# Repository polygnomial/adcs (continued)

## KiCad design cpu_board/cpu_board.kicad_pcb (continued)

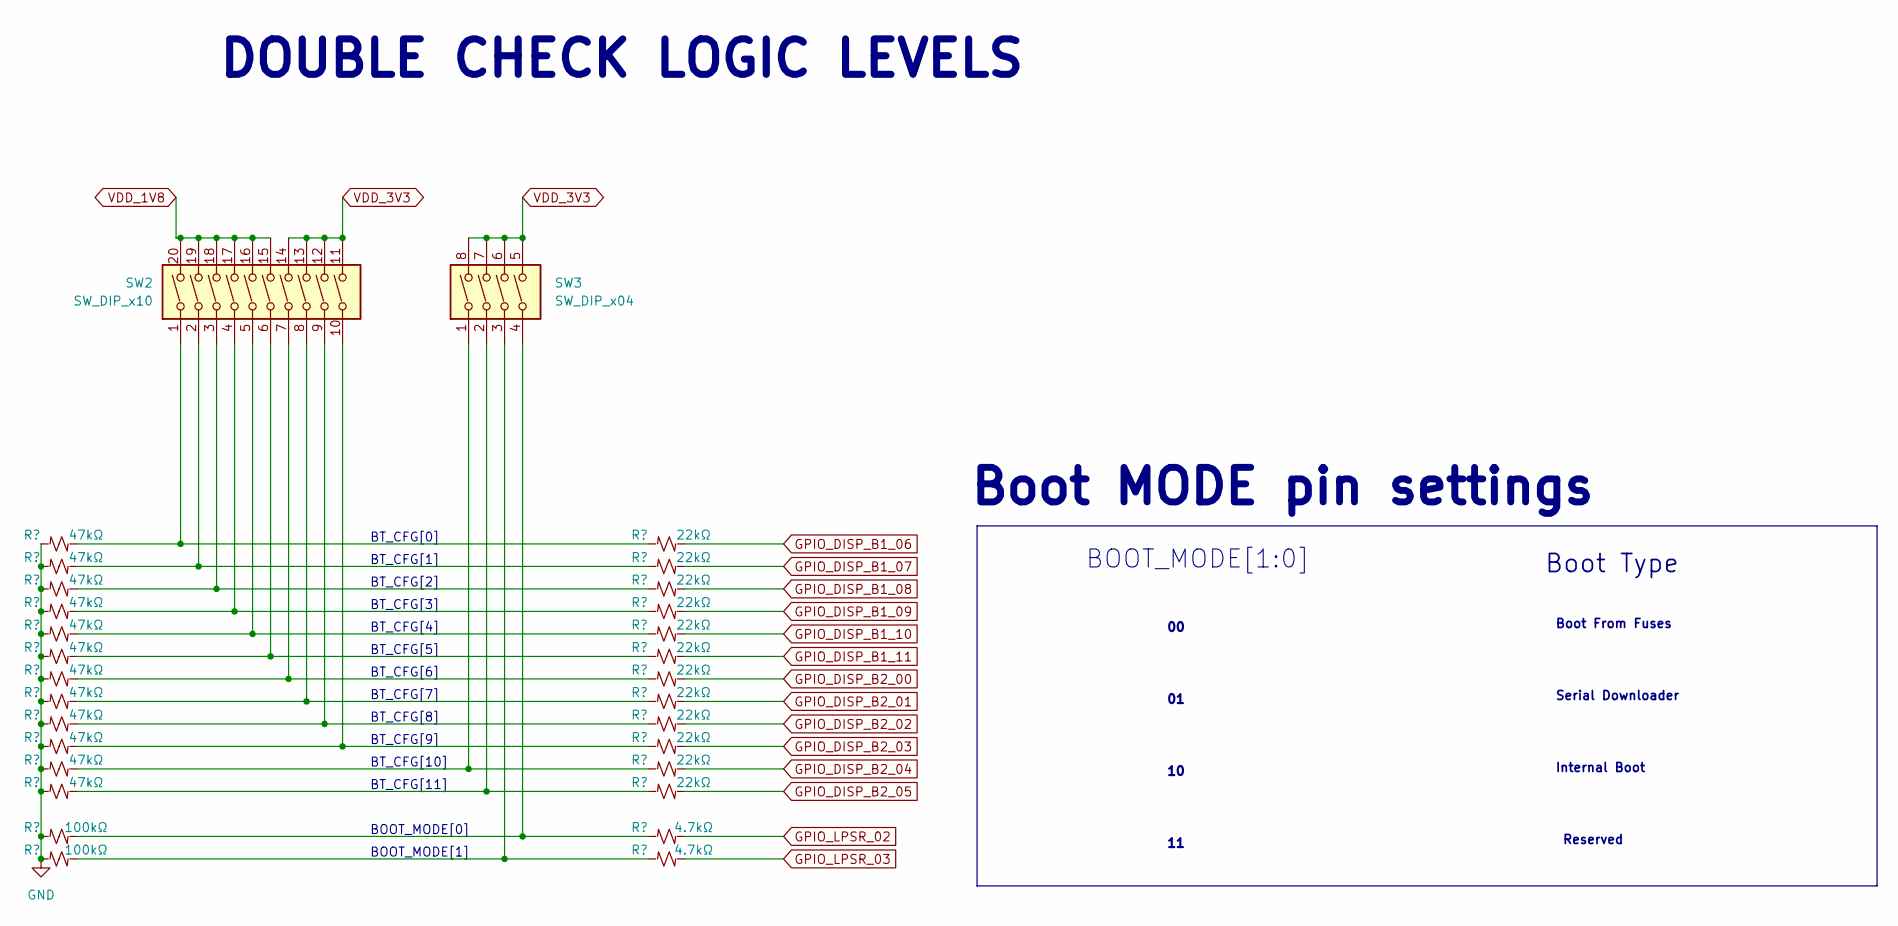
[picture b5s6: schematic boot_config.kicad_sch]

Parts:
R37, R38, R39, R40, R41, R42, R43, R44, R45, R46, R47, R48: 47kΩ; Perfect_0402
R49, R50: 100kΩ; Perfect_0402
R51, R52, R53, R54, R55, R56, R57, R58, R59, R60, R61, R62: 22kΩ; Perfect_0402
R63, R64: 4.7kΩ; Perfect_0402
SW2: SW_DIP_x10; SW-SMD_DSHP10TS-S; JLCPCB P/N Proto C319046
SW3: SW_DIP_x04; SW-SMD_8P-L6.7-W5.4-P1.27-LS8.5; JLCPCB P/N Proto C319050

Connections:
ENET_RGMII_TXC_BT: R56.2; also elsewhere on the board
ENET_RGMII_TXD0_BT: R54.2; also elsewhere on the board
ENET_RGMII_TXD1_BT: R53.2; also elsewhere on the board
ENET_RGMII_TXD2_BT: R52.2; also elsewhere on the board
ENET_RGMII_TXD3_BT: R51.2; also elsewhere on the board
ENET_RGMII_TX_EN_BT: R55.2; also elsewhere on the board
GPIO_DISP_B2_00: R57.2; also elsewhere on the board
GPIO_DISP_B2_01: R58.2; also elsewhere on the board
GPIO_DISP_B2_02: R59.2; also elsewhere on the board
GPIO_DISP_B2_03: R60.2; also elsewhere on the board
GPIO_DISP_B2_04: R61.2; also elsewhere on the board
GPIO_DISP_B2_05: R62.2; also elsewhere on the board
GPIO_LPSR_02: R63.2; also elsewhere on the board
GPIO_LPSR_03: R64.2; also elsewhere on the board
unnamed: R37.2, R51.1, SW2.1
unnamed: R38.2, R52.1, SW2.2
unnamed: R39.2, R53.1, SW2.3
unnamed: R40.2, R54.1, SW2.4
unnamed: R41.2, R55.1, SW2.5
unnamed: R42.2, R56.1, SW2.6
unnamed: R43.2, R57.1, SW2.7
unnamed: R44.2, R58.1, SW2.8
unnamed: R45.2, R59.1, SW2.9
unnamed: R46.2, R60.1, SW2.10
unnamed: R47.2, R61.1, SW3.1
unnamed: R48.2, R62.1, SW3.2
unnamed: R49.2, R63.1, SW3.4
unnamed: R50.2, R64.1, SW3.3
VDD_1V8: SW2.15, SW2.16, SW2.17, SW2.18, SW2.19, SW2.20; also elsewhere on the board
VDD_3V3: SW2.11, SW2.12, SW2.13, SW2.14, SW3.5, SW3.6, SW3.7, SW3.8; also elsewhere on the board

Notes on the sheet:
BOOT_MODE[1]
Internal Boot
DOUBLE CHECK LOGIC LEVELS
BT_CFG[10]
BT_CFG[6]
BT_CFG[8]
Serial Downloader
BT_CFG[2]
BT_CFG[4]
BT_CFG[9]
Boot From Fuses
BT_CFG[1]
Reserved
BT_CFG[0]
BT_CFG[11]
BOOT_MODE[1:0]
BT_CFG[5]
BOOT_MODE[0]
Boot Type
Boot MODE pin settings
BT_CFG[3]
BT_CFG[7]

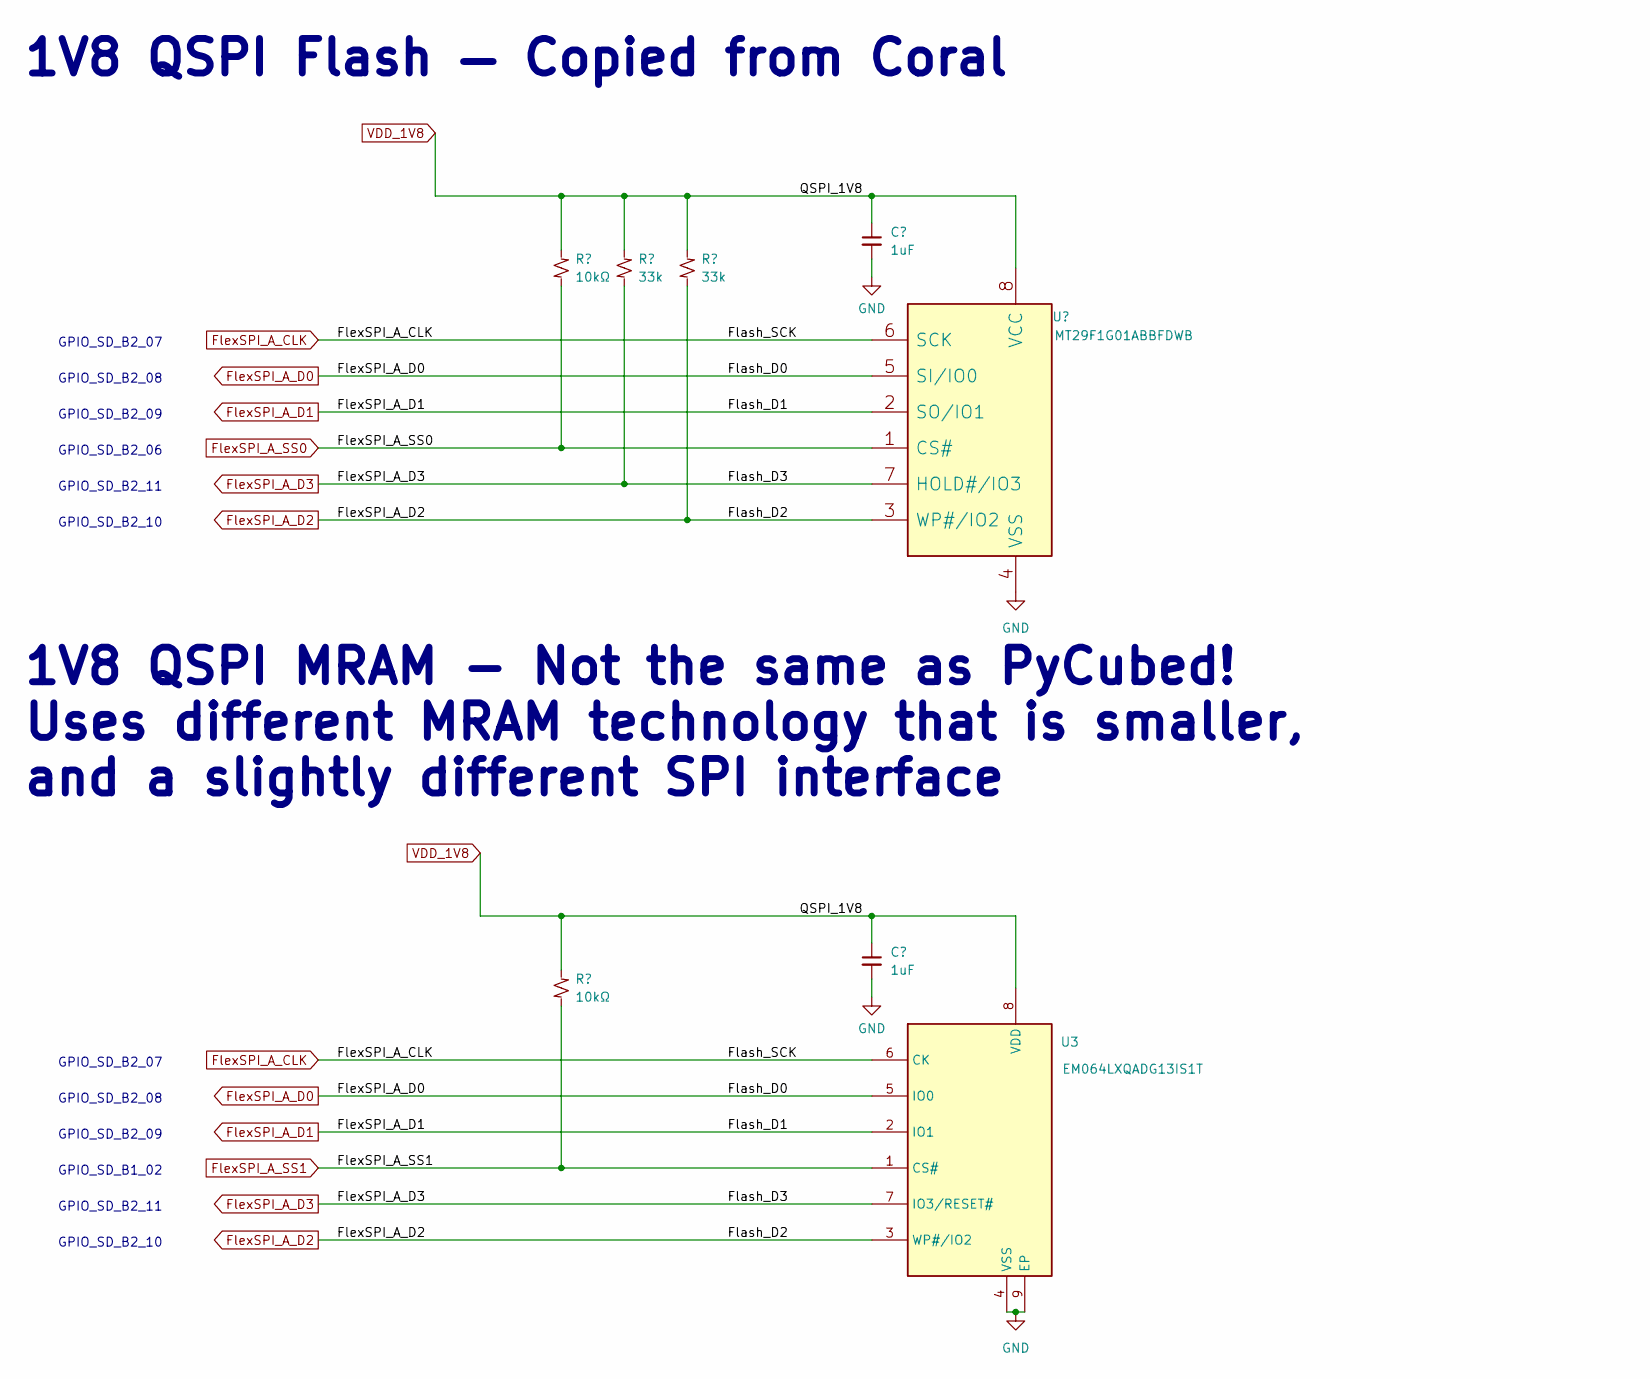
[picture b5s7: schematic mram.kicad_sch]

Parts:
C62, C63: 1uF; Perfect_0402
R16, R17: 10kΩ; Perfect_0402
R18, R20: 33k; Perfect_0402
U3: EM064LXQADG13IS1T; SON127P800X600X95-9N-D
U4: MT29F1G01ABBFDWB; UDFN800X600X65-8; JLCPCB P/N Proto C5330479

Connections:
FlexSPI_A_CLK: U3.6 (CK), U4.6 (SCK); also elsewhere on the board
FlexSPI_A_D0: U3.5 (IO0), U4.5 (SI/IO0); also elsewhere on the board
FlexSPI_A_D1: U3.2 (IO1), U4.2 (SO/IO1); also elsewhere on the board
FlexSPI_A_D2: R20.2, U3.3 (WP#/IO2), U4.3 (WP#/IO2); also elsewhere on the board
FlexSPI_A_D3: R18.2, U3.7 (IO3/RESET#), U4.7 (HOLD#/IO3); also elsewhere on the board
FlexSPI_A_SS0: R16.2, U4.1 (CS#); also elsewhere on the board
FlexSPI_A_SS1: R17.2, U3.1 (CS#); also elsewhere on the board
VDD_1V8: C62.1, C63.1, R16.1, R17.1, R18.1, R20.1, U3.8 (VDD), U4.8 (VCC); also elsewhere on the board

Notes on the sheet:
1V8 QSPI Flash — Copied from Coral
GPIO_SD_B2_10
1V8 QSPI MRAM - Not the same as PyCubed! Uses different MRAM technology that is smaller, and a slightly different SPI interface
GPIO_SD_B2_08
GPIO_SD_B2_06
GPIO_SD_B2_07
GPIO_SD_B1_02
GPIO_SD_B2_09
GPIO_SD_B2_11

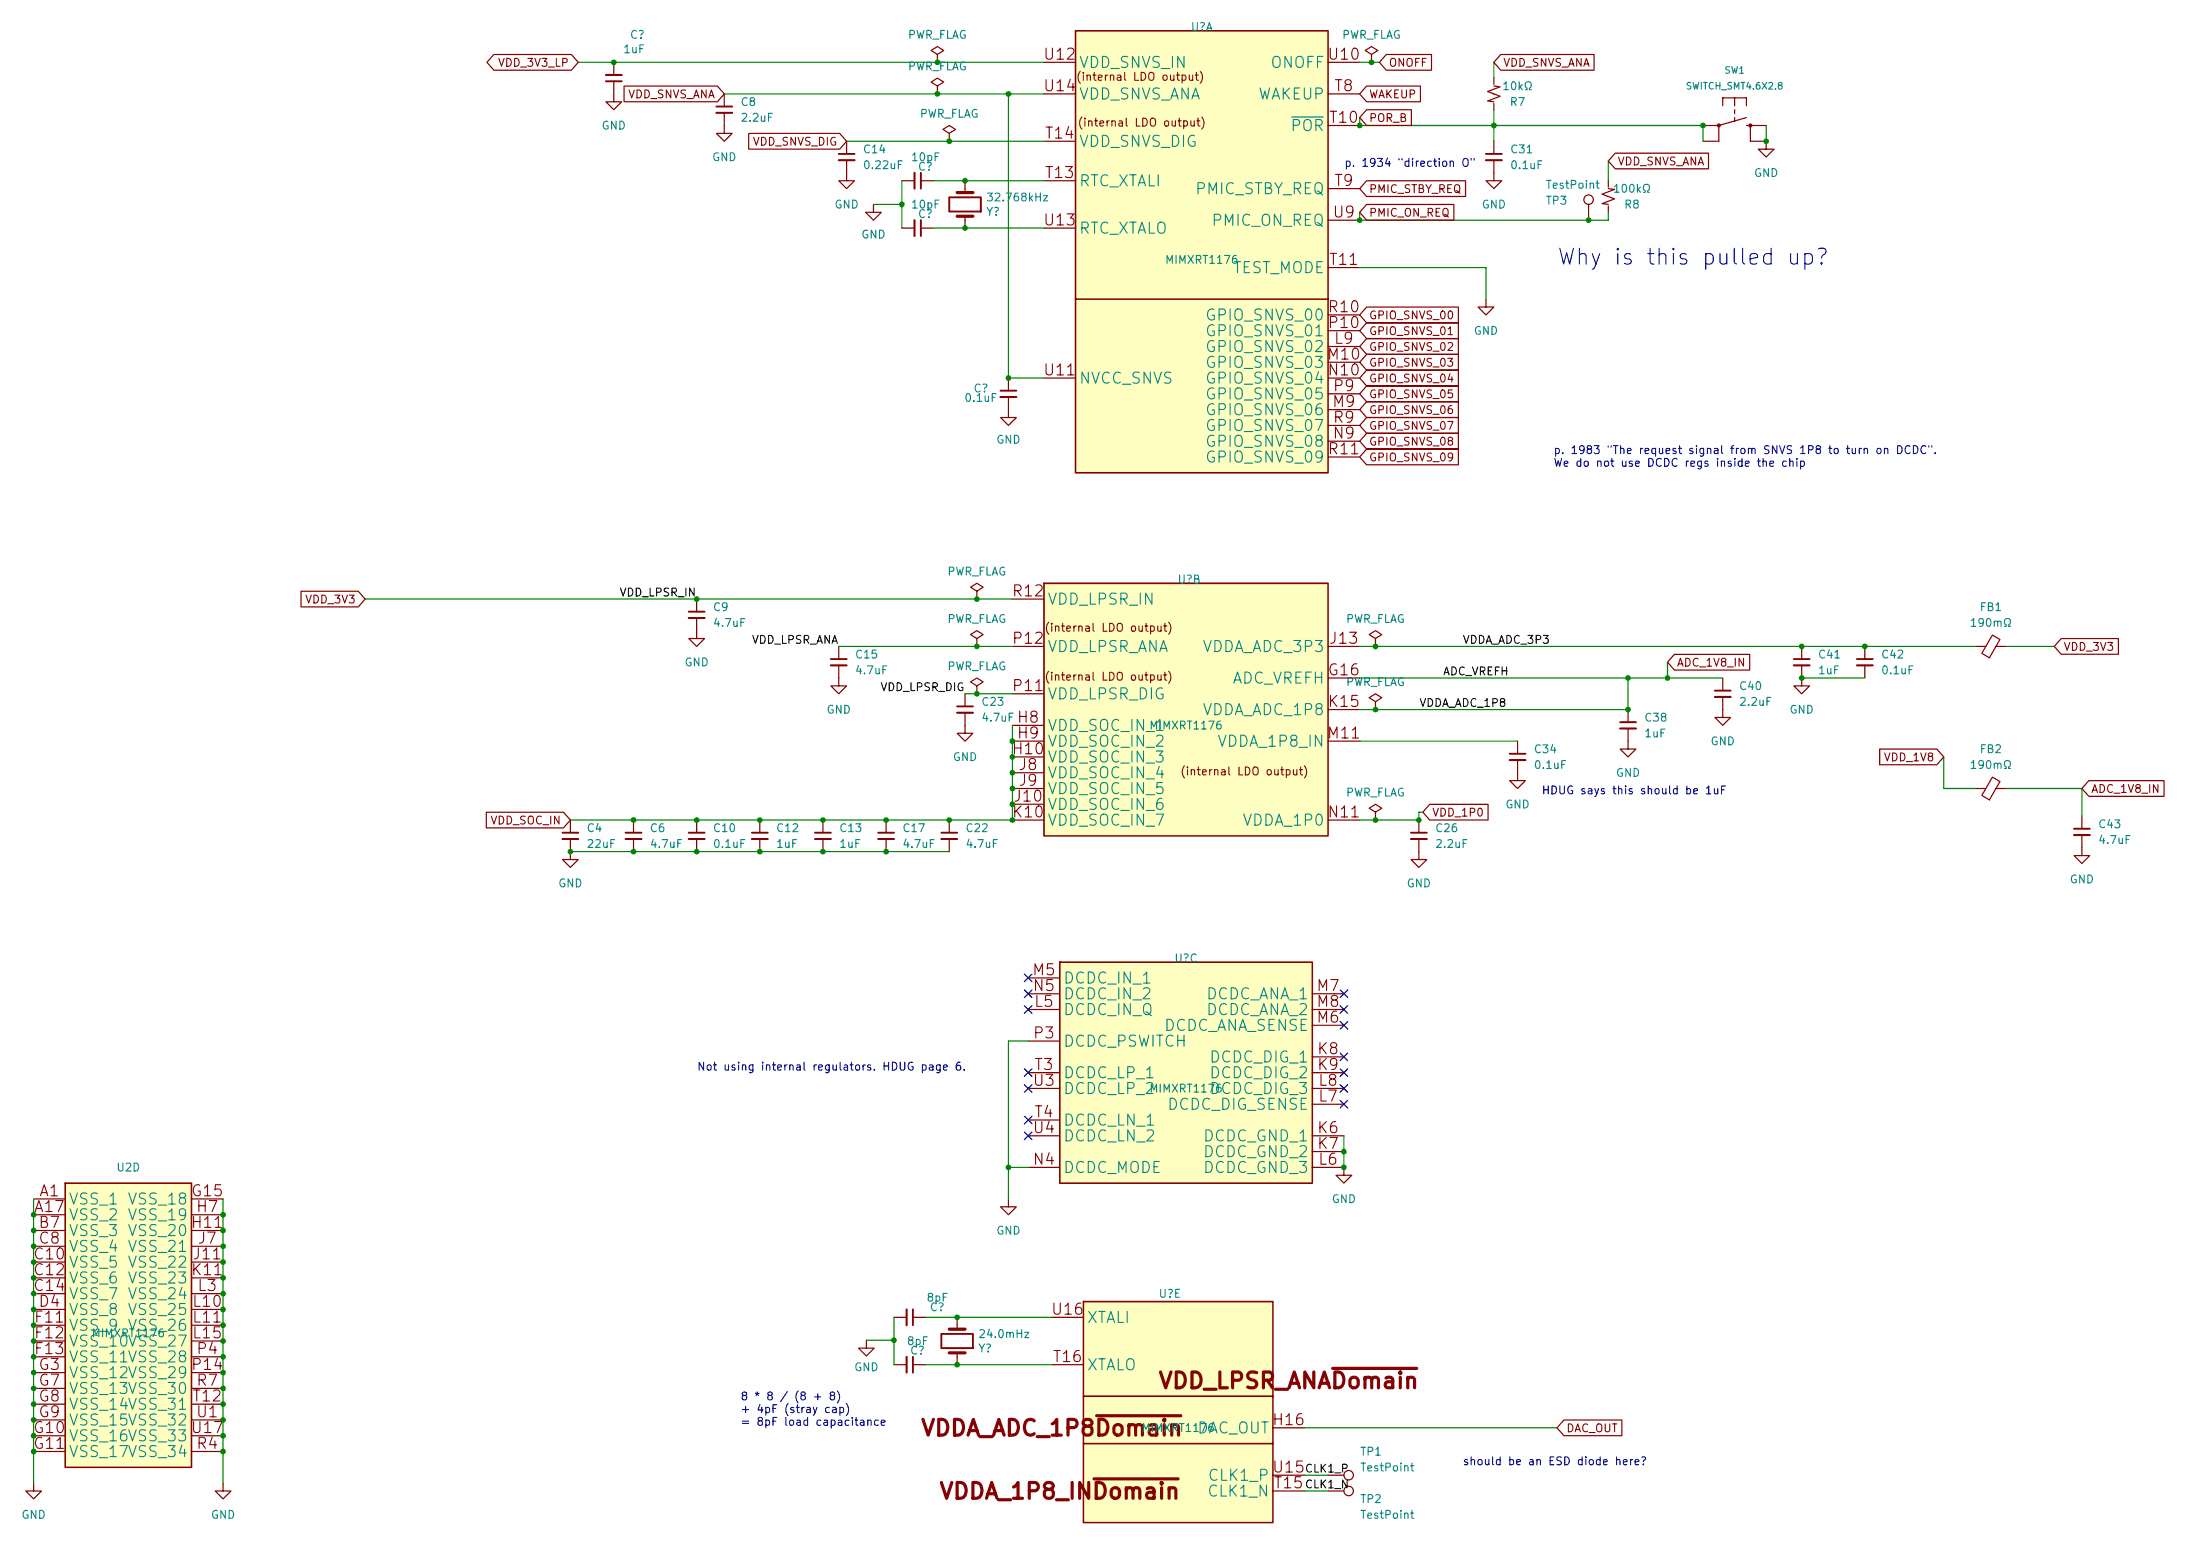
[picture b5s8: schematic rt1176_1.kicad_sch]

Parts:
C3, C12, C13, C38, C41: 1uF; Perfect_0201
C4: 22uF; C_0603_1608Metric
C6: 4.7uF; Perfect_0201; Voltage Rating 6.3V
C8, C26, C40: 2.2uF; Perfect_0201
C9, C15, C17, C22, C23, C43: 4.7uF; Perfect_0201
C10, C25, C34, C42: 0.1uF; Perfect_0201
C14: 0.22uF; Perfect_0201
C18, C19: 8pF; Perfect_0402
C20, C21: 10pF; Perfect_0402
C31: 0.1uF; Perfect_0402
FB1, FB2: 190mΩ; Perfect_0402; JLCPCB P/N C85812
R7: 10kΩ; Perfect_0402
R8: 100kΩ; Perfect_0402
SW1: SWITCH_SMT4.6X2.8; BTN_KMR2_4.6X2.8
TP1, TP2, TP3: TestPoint; TestPoint_Pad_1.0x1.0mm; JLCPCB P/N C221678
U2: MIMXRT1176; U_MIMXRT1176DVMAA_NXP; JLCPCB P/N C1020267
Y2: 24.0mHz; Crystal_SMD_2016-4Pin_2.0x1.6mm; JLCPCB P/N C1986107
Y3: 32.768kHz; Crystal_SMD_3215-2Pin_3.2x1.5mm; JLCPCB P/N C145140

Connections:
/RT1176 #1/CLK1_N: TP2.1, U2.T15 (CLK1_N)
/RT1176 #1/CLK1_P: TP1.1, U2.U15 (CLK1_P)
/RT1176 #1/VDDA_ADC_3P3: C41.1, C42.1, FB1.1, U2.J13 (VDDA_ADC_3P3)
/RT1176 #1/VDD_LPSR_ANA: C15.1, U2.P12 (VDD_LPSR_ANA)
/RT1176 #1/VDD_LPSR_DIG: C23.1, U2.P11 (VDD_LPSR_DIG)
ADC_1V8_IN: C38.1, C40.1, C43.1, FB2.2, U2.G16 (ADC_VREFH), U2.K15 (VDDA_ADC_1P8)
DAC_OUT: U2.H16 (DAC_OUT); also elsewhere on the board
GPIO_SNVS_00: U2.R10 (GPIO_SNVS_00); also elsewhere on the board
GPIO_SNVS_01: U2.P10 (GPIO_SNVS_01); also elsewhere on the board
GPIO_SNVS_02: U2.L9 (GPIO_SNVS_02); also elsewhere on the board
GPIO_SNVS_03: U2.M10 (GPIO_SNVS_03); also elsewhere on the board
GPIO_SNVS_04: U2.N10 (GPIO_SNVS_04); also elsewhere on the board
GPIO_SNVS_05: U2.P9 (GPIO_SNVS_05); also elsewhere on the board
GPIO_SNVS_06: U2.M9 (GPIO_SNVS_06); also elsewhere on the board
GPIO_SNVS_07: U2.R9 (GPIO_SNVS_07); also elsewhere on the board
GPIO_SNVS_08: U2.N9 (GPIO_SNVS_08); also elsewhere on the board
GPIO_SNVS_09: U2.R11 (GPIO_SNVS_09); also elsewhere on the board
unnamed: C20.1, U2.T13 (RTC_XTALI), Y3.2
unnamed: C21.1, U2.U13 (RTC_XTALO), Y3.1
unnamed: C34.1, U2.M11 (VDDA_1P8_IN)
unnamed: C18.1, U2.U16 (XTALI), Y2.2
unnamed: C19.1, U2.T16 (XTALO), Y2.1
ONOFF: U2.U10 (ONOFF); also elsewhere on the board
PMIC_ON_REQ: R8.1, TP3.1, U2.U9 (PMIC_ON_REQ); also elsewhere on the board
PMIC_STBY_REQ: U2.T9 (PMIC_STBY_REQ); also elsewhere on the board
POR_B: C31.1, R7.1, SW1.A, SW1.A' (P1), U2.T10 (~POR); also elsewhere on the board
VDD_1P0: C26.1, U2.N11 (VDDA_1P0)
VDD_1V8: FB2.1; also elsewhere on the board
VDD_3V3: C9.1, FB1.2, U2.R12 (VDD_LPSR_IN); also elsewhere on the board
VDD_SNVS_ANA: C8.1, C25.1, R7.2, R8.2, U2.U11 (NVCC_SNVS), U2.U14 (VDD_SNVS_ANA); also elsewhere on the board
VDD_SNVS_DIG: C14.1, U2.T14 (VDD_SNVS_DIG)
VDD_SOC_IN: C4.1, C6.1, C10.1, C12.1, C13.1, C17.1, C22.1, U2.H8 (VDD_SOC_IN_1), U2.H9 (VDD_SOC_IN_2), U2.H10 (VDD_SOC_IN_3), U2.J8 (VDD_SOC_IN_4), U2.J9 (VDD_SOC_IN_5), U2.J10 (VDD_SOC_IN_6), U2.K10 (VDD_SOC_IN_7)
WAKEUP: U2.T8 (WAKEUP); also elsewhere on the board

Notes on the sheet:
8 * 8 / (8 + 8) + 4pF (stray cap) = 8pF load capacitance
Not using internal regulators. HDUG page 6.
should be an ESD diode here?
p. 1983 "The request signal from SNVS 1P8 to turn on DCDC". We do not use DCDC regs inside the chip
Why is this pulled up?
HDUG says this should be 1uF
p. 1934 "direction O"

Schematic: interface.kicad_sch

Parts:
H1, H2, H3, H4: MountingHole_Pad; MountingHole_2.7mm_M2.5_DIN965_Pad
J2, J4: 353620650; MOLEX_35362-0650
J3: JTAG_SWD_10; PinHeader_2x05_P1.27mm_Vertical_SMD; JLCPCB P/N C180221
J5: Conn_01x06; PinHeader_1x06_P2.54mm_Vertical
R4, R33: 10kΩ; Perfect_0402

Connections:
EN_ADCS: J4.3, J5.2; also elsewhere on the board
EN_LP: J4.2, R4.2; also elsewhere on the board
GNDREF: J5.4; also elsewhere on the board
JTAG_TDI: J3.8 (NC/TDI); also elsewhere on the board
JTAG_TDO: J3.6 (SWO/TDO); also elsewhere on the board
unnamed: J5.1, R33.2
POR_B: J4.1; also elsewhere on the board
P_GOOD: J4.4; also elsewhere on the board
RT1176_RX_FROM_HOST: J4.6
RT1176_TX_TO_HOST: J4.5
SWD_CLK: J3.4 (SWDCLK/TCK); also elsewhere on the board
SWD_DIO: J3.2 (SWDIO/TMS); also elsewhere on the board
SWD_RESET: J3.10 (~RESET); also elsewhere on the board
VBATT_IN: J2.1, J2.3, J2.5, J5.5; also elsewhere on the board
VDD_3V3: J3.1 (VTref); also elsewhere on the board
VUSB: J5.6; also elsewhere on the board

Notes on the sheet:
1. Add jumper keep board enabled without mainboard
REMOVE ALL JUMPERS BEFORE FLIGHT
Connector allows RBF placement on a side panel
SWD
"GND"
Control and I/O Harness
"VUSB"
2-3. Add jumpers to allow USB to power board.
RBF Harness
Battery Power Harness
"EN"
Mounting Holes

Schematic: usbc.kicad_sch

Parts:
C66: 4.7uF; Perfect_0402
J1: USB_C_pycubed; USB_C_Receptacle_XKB_U262-161N-4BVC11; JLCPCB P/N C319148
L2: DLW21HN900SQ2L; IND4_CHOKE_0805; JLCPCB P/N C80529
R22, R23: 5.1kΩ; Perfect_0402
TP8, TP9: TestPoint
U5: USBLC6-2SC6; SOT23-6L_STM; JLCPCB P/N C2687116

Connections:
/USB-C/USB_CON_DN: J1.A7 (D-), J1.B7 (D-), U5.1 (IO_1_IN)
/USB-C/USB_CON_DP: J1.A6 (D+), J1.B6 (D+), U5.3 (IO_2_IN)
GNDREF: C66.2, J1.A1 (GND), J1.A12 (GND), J1.S1 (SHIELD), R22.1, R23.1; also elsewhere on the board
unnamed: L2.4, U5.6 (IO_1_OUT)
unnamed: L2.1, U5.4 (IO_2_OUT)
OTG1_D_N: L2.2, TP8.1; also elsewhere on the board
OTG1_D_P: L2.3, TP9.1; also elsewhere on the board
USB_CC1: J1.A5 (CC1), R23.2
USB_CC2: J1.B5 (CC2), R22.2
VUSB: C66.1, J1.A4 (VBUS), J1.A9 (VBUS), U5.5 (VBUS); also elsewhere on the board

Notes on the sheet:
New isolation diodes (not on PyCubed)
90ohm differential pairs

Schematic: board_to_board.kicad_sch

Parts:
J6, J7: DF40C-100DP-0.4V(51); DF40C100DP04V51; JLCPCB P/N C531031

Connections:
BT_CFG_IO_EN: J6.37; also elsewhere on the board
CAMERA_TRIG: J7.81; also elsewhere on the board
DAC_OUT: J6.20; also elsewhere on the board
ENET_RGMII_MDC: J7.85; also elsewhere on the board
ENET_RGMII_MDIO: J7.87; also elsewhere on the board
ENET_RGMII_RXC: J7.22; also elsewhere on the board
ENET_RGMII_RXD0: J7.24; also elsewhere on the board
ENET_RGMII_RXD1: J7.26; also elsewhere on the board
ENET_RGMII_RXD2: J7.28; also elsewhere on the board
ENET_RGMII_RXD3: J7.30; also elsewhere on the board
ENET_RGMII_RX_EN: J7.20; also elsewhere on the board
ENET_RGMII_TXC_BT: J7.44; also elsewhere on the board
ENET_RGMII_TXD0_BT: J7.40; also elsewhere on the board
ENET_RGMII_TXD1_BT: J7.38; also elsewhere on the board
ENET_RGMII_TXD2_BT: J7.36; also elsewhere on the board
ENET_RGMII_TXD3_BT: J7.34; also elsewhere on the board
ENET_RGMII_TX_EN_BT: J7.42; also elsewhere on the board
EN_ADCS: J6.22; also elsewhere on the board
GPIO_AD_00: J6.25; also elsewhere on the board
GPIO_AD_01: J6.27; also elsewhere on the board
GPIO_AD_02: J6.31; also elsewhere on the board
GPIO_AD_03: J6.33; also elsewhere on the board
GPIO_AD_04: J6.35; also elsewhere on the board
GPIO_AD_06: J6.41; also elsewhere on the board
GPIO_AD_07: J6.43; also elsewhere on the board
GPIO_AD_08: J6.45; also elsewhere on the board
GPIO_AD_09: J6.47; also elsewhere on the board
GPIO_AD_10: J6.51; also elsewhere on the board
GPIO_AD_11: J6.53; also elsewhere on the board
GPIO_AD_12: J6.55; also elsewhere on the board
GPIO_AD_13: J6.57; also elsewhere on the board
GPIO_AD_14: J6.61; also elsewhere on the board
GPIO_AD_15: J6.63; also elsewhere on the board
GPIO_AD_16: J6.65; also elsewhere on the board
GPIO_AD_17: J6.67; also elsewhere on the board
GPIO_AD_18: J6.71; also elsewhere on the board
GPIO_AD_19: J6.73; also elsewhere on the board
GPIO_AD_20: J6.75; also elsewhere on the board
GPIO_AD_21: J6.77; also elsewhere on the board
GPIO_AD_22: J6.83; also elsewhere on the board
GPIO_AD_23: J6.81; also elsewhere on the board
GPIO_AD_26: J6.87; also elsewhere on the board
GPIO_AD_27: J6.91; also elsewhere on the board
GPIO_AD_28: J6.93; also elsewhere on the board
GPIO_AD_29: J6.95; also elsewhere on the board
GPIO_AD_30: J6.97; also elsewhere on the board
GPIO_AD_31: J6.90; also elsewhere on the board
GPIO_AD_32: J6.92; also elsewhere on the board
GPIO_AD_33: J6.94; also elsewhere on the board
GPIO_AD_34: J6.96; also elsewhere on the board
GPIO_AD_35: J6.98; also elsewhere on the board
GPIO_DISP_B2_00: J7.48; also elsewhere on the board
GPIO_DISP_B2_01: J7.50; also elsewhere on the board
GPIO_DISP_B2_02: J7.52; also elsewhere on the board
GPIO_DISP_B2_03: J7.54; also elsewhere on the board
GPIO_DISP_B2_04: J7.56; also elsewhere on the board
GPIO_DISP_B2_05: J7.58; also elsewhere on the board
GPIO_DISP_B2_06: J7.62; also elsewhere on the board
GPIO_DISP_B2_07: J7.64; also elsewhere on the board
GPIO_DISP_B2_08: J7.66; also elsewhere on the board
GPIO_DISP_B2_09: J7.68; also elsewhere on the board
GPIO_DISP_B2_10: J7.70; also elsewhere on the board
GPIO_DISP_B2_11: J7.74; also elsewhere on the board
GPIO_DISP_B2_12: J7.76; also elsewhere on the board
GPIO_DISP_B2_13: J7.78; also elsewhere on the board
GPIO_DISP_B2_14: J7.80; also elsewhere on the board
GPIO_DISP_B2_15: J7.82; also elsewhere on the board
GPIO_EMC_B1_40: J6.52; also elsewhere on the board
GPIO_EMC_B1_41: J6.54; also elsewhere on the board
GPIO_EMC_B2_00: J7.41; also elsewhere on the board
GPIO_EMC_B2_01: J7.43; also elsewhere on the board
GPIO_EMC_B2_02: J7.45; also elsewhere on the board
GPIO_EMC_B2_03: J7.47; also elsewhere on the board
GPIO_EMC_B2_04: J7.49; also elsewhere on the board
GPIO_EMC_B2_05: J7.53; also elsewhere on the board
GPIO_EMC_B2_06: J7.55; also elsewhere on the board
GPIO_EMC_B2_07: J7.57; also elsewhere on the board
GPIO_EMC_B2_08: J7.59; also elsewhere on the board
GPIO_EMC_B2_09: J7.61; also elsewhere on the board
GPIO_EMC_B2_10: J7.65; also elsewhere on the board
GPIO_EMC_B2_11: J7.67; also elsewhere on the board
GPIO_EMC_B2_12: J7.69; also elsewhere on the board
GPIO_EMC_B2_13: J7.71; also elsewhere on the board
GPIO_EMC_B2_14: J7.73; also elsewhere on the board
GPIO_EMC_B2_15: J7.77; also elsewhere on the board
GPIO_EMC_B2_16: J7.79; also elsewhere on the board
GPIO_EMC_B2_18: J7.83; also elsewhere on the board
GPIO_LPSR_00: J6.1; also elsewhere on the board
GPIO_LPSR_01: J6.3; also elsewhere on the board
GPIO_LPSR_02: J6.5; also elsewhere on the board
GPIO_LPSR_03: J6.7; also elsewhere on the board
GPIO_LPSR_04: J6.11; also elsewhere on the board
GPIO_LPSR_05: J6.13; also elsewhere on the board
GPIO_LPSR_06: J6.15; also elsewhere on the board
GPIO_LPSR_07: J6.17; also elsewhere on the board
GPIO_LPSR_08: J6.21; also elsewhere on the board
GPIO_LPSR_09: J6.23; also elsewhere on the board
GPIO_SD_B1_00: J6.26; also elsewhere on the board
GPIO_SD_B1_01: J6.28; also elsewhere on the board
GPIO_SD_B1_03: J6.30; also elsewhere on the board
GPIO_SD_B1_04: J6.32; also elsewhere on the board
GPIO_SD_B1_05: J6.34; also elsewhere on the board
GPIO_SNVS_00: J7.17; also elsewhere on the board
GPIO_SNVS_01: J7.19; also elsewhere on the board
GPIO_SNVS_02: J7.21; also elsewhere on the board
GPIO_SNVS_03: J7.23; also elsewhere on the board
GPIO_SNVS_04: J7.25; also elsewhere on the board
GPIO_SNVS_05: J7.29; also elsewhere on the board
GPIO_SNVS_06: J7.31; also elsewhere on the board
GPIO_SNVS_07: J7.33; also elsewhere on the board
GPIO_SNVS_08: J7.35; also elsewhere on the board
GPIO_SNVS_09: J7.37; also elsewhere on the board
LPUART1_RX_BOOT: J6.85; also elsewhere on the board
ONOFF: J6.12; also elsewhere on the board
PMIC_ON_REQ: J6.18; also elsewhere on the board
PMIC_STBY_REQ: J6.14; also elsewhere on the board
USDHC2_CLK: J6.46; also elsewhere on the board
USDHC2_CMD: J6.48; also elsewhere on the board
USDHC2_DATA0: J6.44; also elsewhere on the board
USDHC2_DATA1: J6.42; also elsewhere on the board
USDHC2_DATA2: J6.40; also elsewhere on the board
USDHC2_DATA3: J6.38; also elsewhere on the board
VDD_1V8: J7.9, J7.10, J7.11, J7.12, J7.13, J7.14, J7.15, J7.16; also elsewhere on the board
VDD_3V3: J6.2, J6.4, J6.6, J6.8, J7.1, J7.2, J7.3, J7.4, J7.5, J7.6, J7.7, J7.8; also elsewhere on the board
WAKEUP: J6.16; also elsewhere on the board

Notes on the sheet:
1V8
This is still a little bit messy and I need to double check all the labels I do not think DRC catches global labels that are only present in one spot (since I left some of the "ethernet" labels, etc. and there are no errors for those)
GPIO_DISP_B1_06 to 11 & GPIO_DISP_B2_00 to 05 NOT FOR GENERAL USE Requires special consideration to avoid driving these at boot, or board may fail to boot
DF40C-100DP-0.4V(51)

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
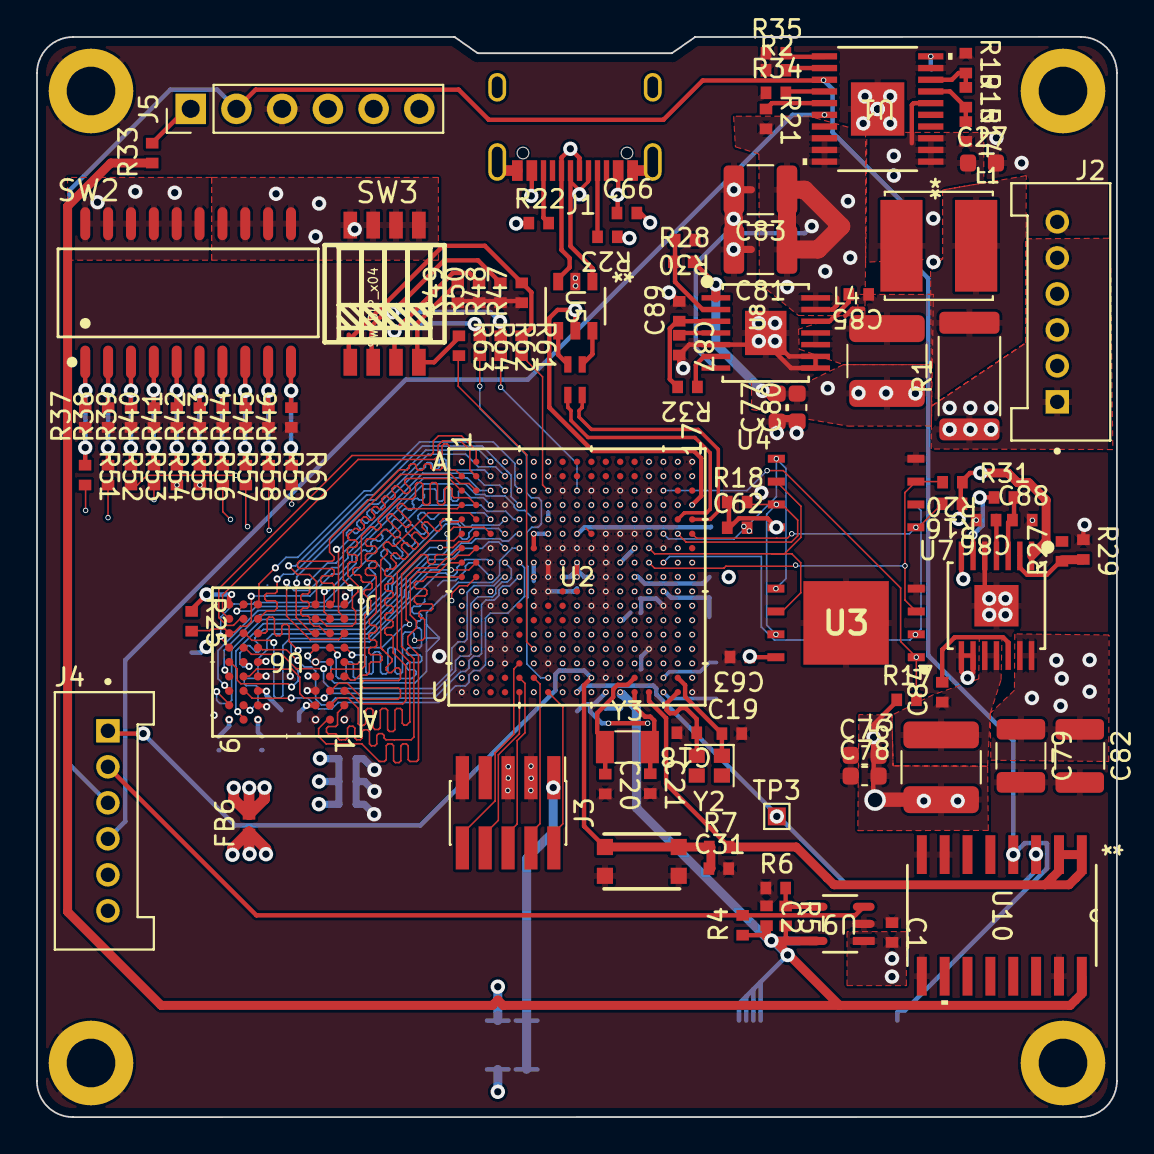
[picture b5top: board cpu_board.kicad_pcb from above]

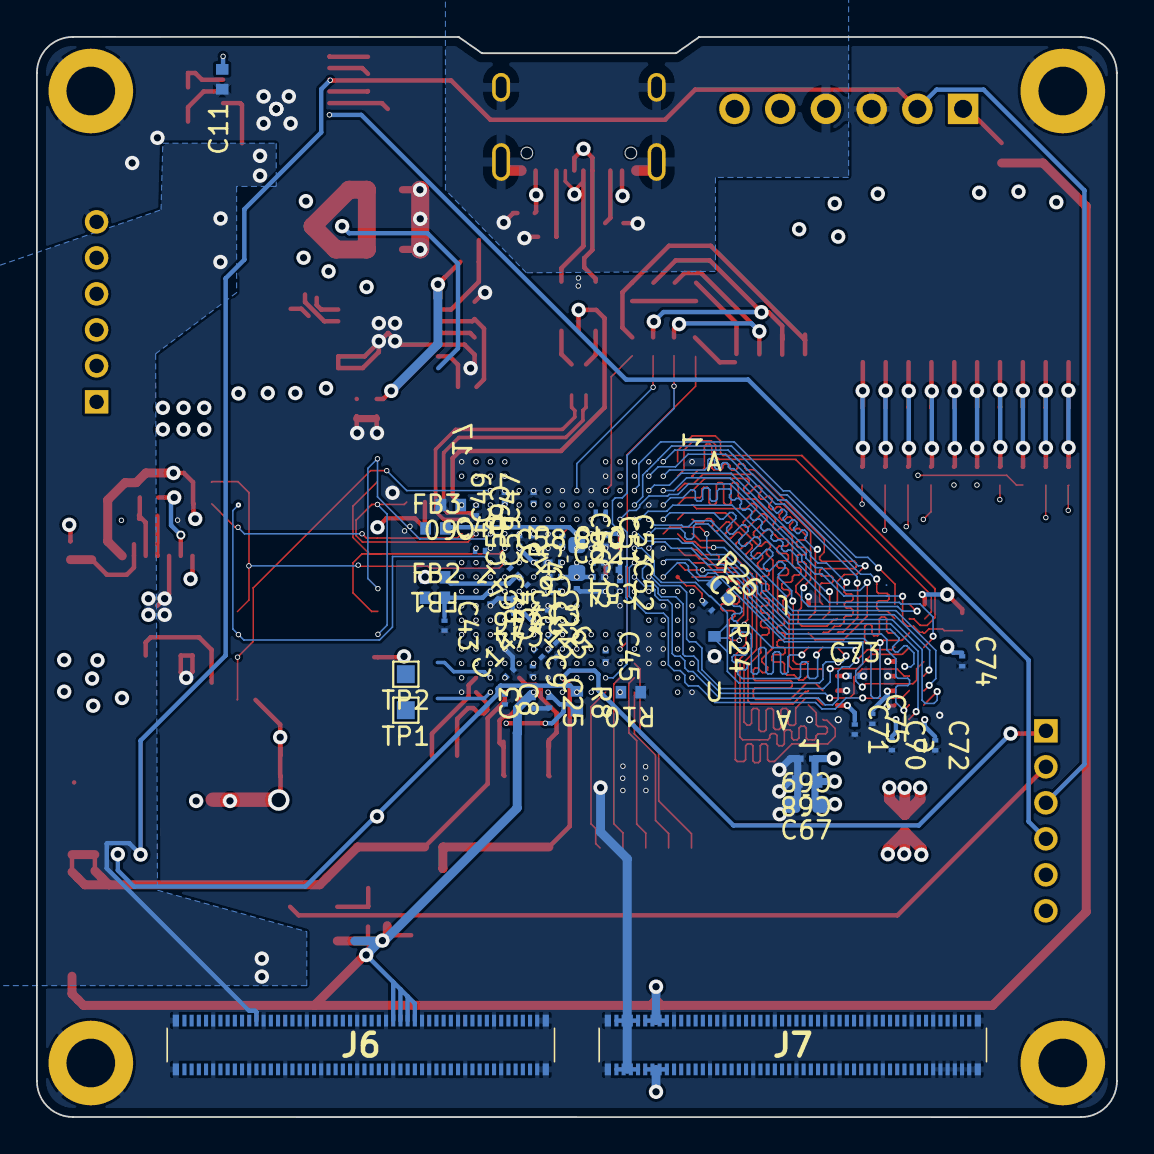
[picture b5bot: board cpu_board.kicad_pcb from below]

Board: 6 copper layers, 60.0 x 60.0 mm, 169 parts (60 on the bottom side), 252 nets.

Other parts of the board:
C11: 22nF; Perfect_0402
L1: 330uH; IND_SRN6045TA-331K
R2: 0Ω; Perfect_0402
R3: 10kΩ; Perfect_0201
R14: 800kΩ; Perfect_0402
R15, R19: 100kΩ; Perfect_0402
R21: 10kΩ; Perfect_0402
R34: 30kΩ; Perfect_0402
R35: 18kΩ; Perfect_0402

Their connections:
VBATT_SENSE: L1.1; also elsewhere on the board

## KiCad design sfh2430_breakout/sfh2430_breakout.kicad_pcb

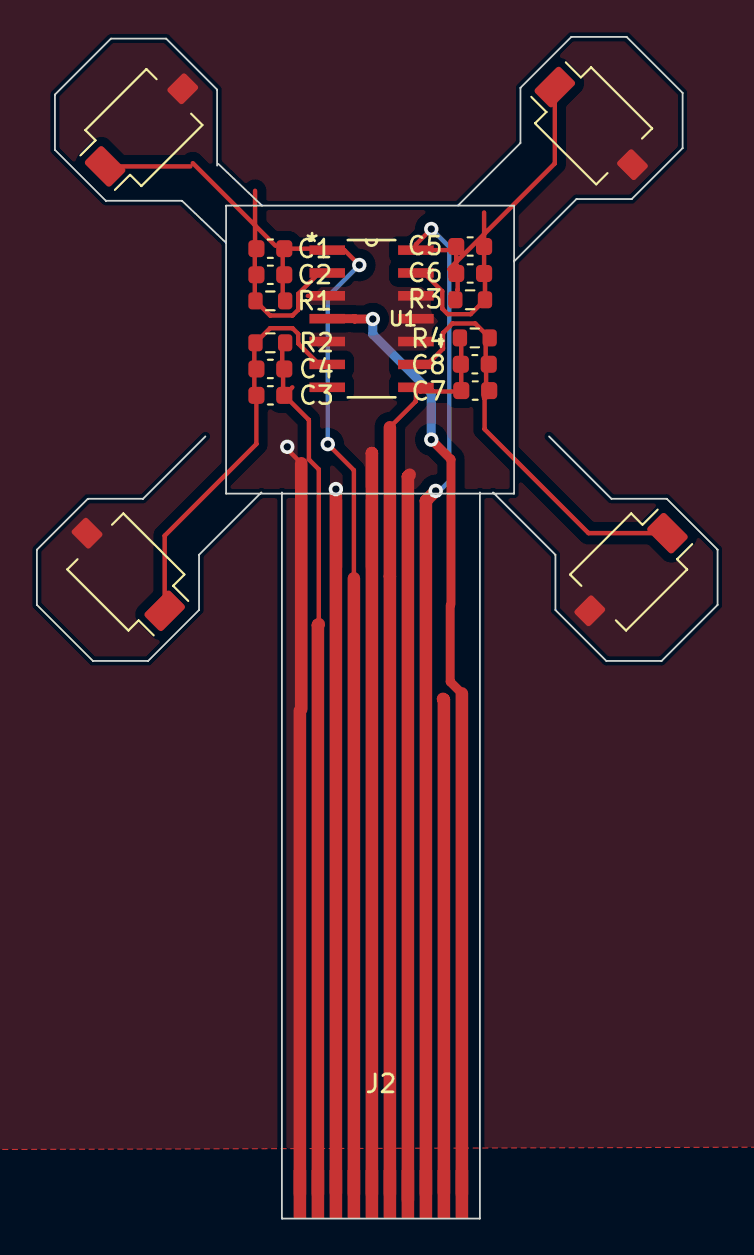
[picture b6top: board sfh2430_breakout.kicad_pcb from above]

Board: 2 copper layers, 37.8 x 65.6 mm, 18 parts (0 on the bottom side), 10 nets.

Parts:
C1, C3, C5, C7: 1nF; C_0603_1608Metric
C2, C4, C6, C8: 100nF; C_0603_1608Metric
D1, D2, D3, D4: SFH2430; Osram_SFH2430
J2: Conn_01x10; 10pin_1mm_pitch_flat_flex
R1, R2, R3, R4: 3.9k; R_0603_1608Metric
U1: LTC2052IS_PBF; SO-14_S

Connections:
+3V3: J2.10, U1.4 (V+)
/OUT1: C1.2, C2.2, J2.4, R1.2, U1.1 (OUTA)
/OUT2: C3.2, C4.2, J2.2, R2.2, U1.7 (OUTB)
/OUT3: C7.2, C8.2, J2.6, R4.2, U1.8 (OUTC)
/OUT4: C5.2, C6.2, J2.8, R3.2, U1.14 (OUTD)
/Photodiode 1/IN-: C1.1, C2.1, D1.1 (K), R1.1, U1.2 (-INA)
/Photodiode 2/IN-: C3.1, C4.1, D2.1 (K), R2.1, U1.6 (-INB)
/Photodiode 3/IN-: C7.1, C8.1, D4.1 (K), R4.1, U1.9 (-INC)
/Photodiode 4/IN-: C5.1, C6.1, D3.1 (K), R3.1, U1.13 (-IND)
GND: D1.2 (A), D2.2 (A), D3.2 (A), D4.2 (A), J2.1, J2.3, J2.5, J2.7, J2.9, U1.3 (+INA), U1.5 (+INB), U1.10 (+INC), U1.11 (V-), U1.12 (+IND)
